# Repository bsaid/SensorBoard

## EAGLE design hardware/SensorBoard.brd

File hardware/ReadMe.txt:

ESP32 Sensor board:

Popis desky:
- dvě desky jako sendvič 50 mm * 31 mm * 13 mm
- propojení desek lze využít jako konektor pro připojení dalších periferií
- 3 možnosti bezdrátového připojení + USB

Vlastnosti:
- vlastní LiPoly baterie se správou napájení a nabíjením přes USB
- USB FTDI
- 80 MHz procesor
- micro SD karta standard 3.0 (lze >32 GB)
- 14 pinů pro připojení volitelných periferií, i výstupních (serva, LED, DAC reproduktor)
- Bluetooth 4.0 nebo WiFi připojení, lze v jeden okamžik používat jen jedno
- 433 nebo 868 MHz radio pro komunikaci na vzdálenost do 1.5 km nebo pro komunikaci skrz biologický materiál (tělo koně)
- citlivá elektronika ukrytá uvnitř sendviče
- 2 tlačítka
- 2 SW LED (+ několik HW LED)
- adapter na magnetický USB-C pro lepší utěsnění proti prachu
- možnost připojit senzor srdečního tepu, dechu, saturace krve kyslíkem (po konzultaci s Monet+)

Senzory:
- akcelerometr
- gyroskop
- kompas
- vlhkoměr
- barometr
- teploměr
- externě GPS, instenzita světla, mikrofon

Navíc:
- deska má dostatek senzorů, výkonu na procesoru a vyvedených konektorů na to, aby šla naprogramovat jako jednoduchý autopilot
- návrh jsem zamýšlel i jako univerzální desku pro vývoj na ESP32 procesorech s některými senzory jako bonus
- 2x DAC (třeba pro příjem a přehrání zvuku)

Problémy během návrhu:
- dostatečně malá deska, která nebude zvířeti zavazet
- chybějící kondenzátor na pinu EN způsoboval nepředvídatelné chování a občas úplnou nefunkčnost procesoru ESP32
- těžko sehnatelná ručně pájitelná pouzdra senzorů
- výběr vhodného čipu pro správu napájení, stále slabé místo, nevyzkoušené předem
- komunikace s firmou a získání relevantních informací a požadavků

Seznam součástek je v samostatném souboru.
Původní zadání a high-level požadavky jsou v samostatném souboru.
Všechny použité součástky jsou uloženy jako samostatné knihovny ve složce lib.

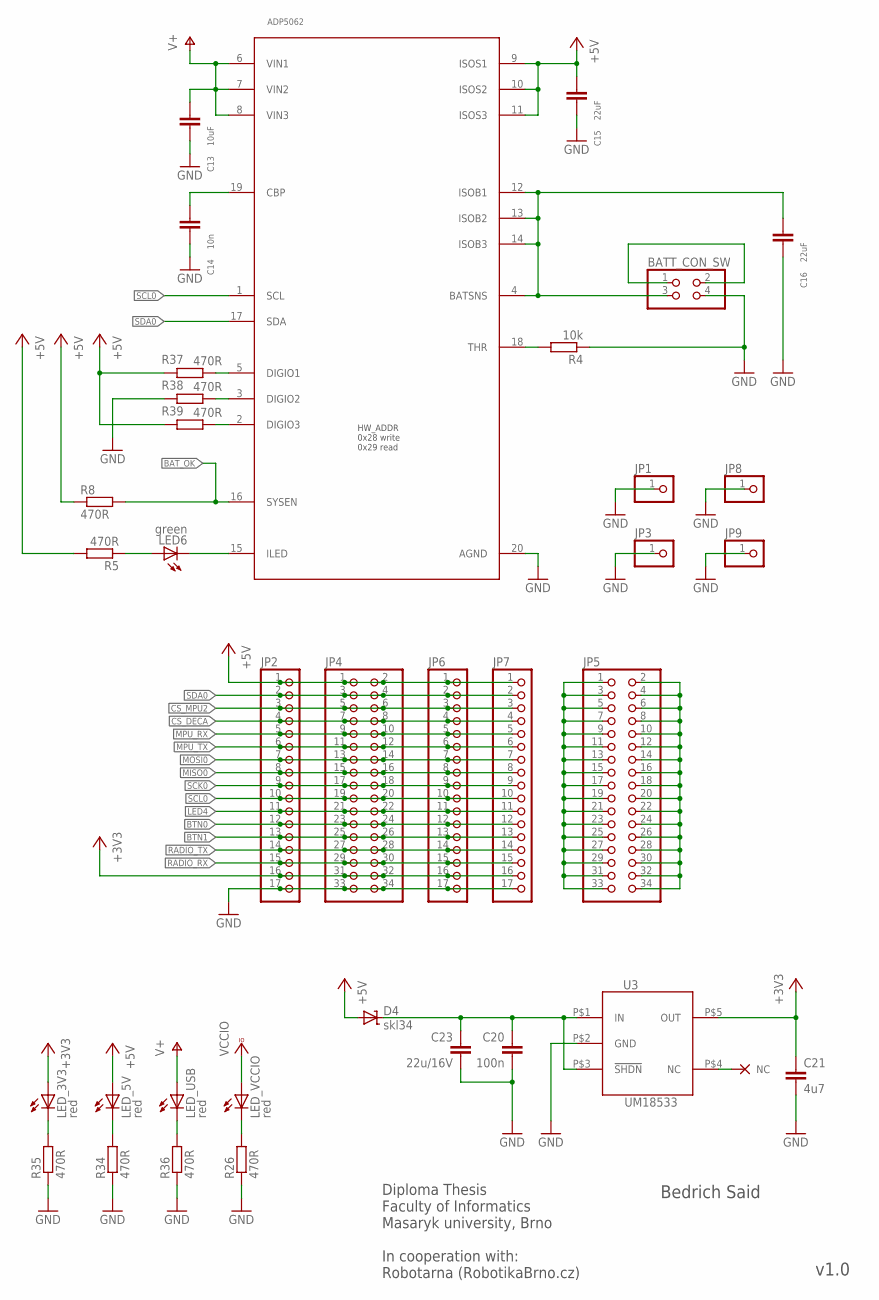
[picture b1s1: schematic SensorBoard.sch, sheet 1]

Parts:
BATT_CON_SW: PINHD-2X2; 2X02
C13: 10uF; C1206
C14: 10n; C0603
C15, C16: 22uF; C1206
C20: 100n; C0603
C21: 4u7; C0603
C23: 22u/16V; C1206
CHARGER: ADP5062; QFN50P400X400X80-21N
D4: skl34; SOD123
JP1, JP3, JP8, JP9: PINHD-1X1; 1X01
JP2, JP6, JP7: PINHD-1X17; 1X17
JP4, JP5: PINHD-2X17; 2X17
LED6: green; CHIPLED_0603
LED_3V3, LED_5V: red; CHIPLED_0603
LED_USB: red; CHIPLED_0603
LED_VCCIO: red; CHIPLED_0603
R4: 10k; R0603
R5, R8, R26, R34, R35, R36, R37, R38, R39: 470R; R0603
U3: UM18533; SOT23-5

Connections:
5V->3V3: C20.1, C23.1, D4.C, U3.P$1 (IN), U3.P$3 (!SHDN)
+3V3: C21.1, JP2.16, JP4.31, JP4.32, JP6.16, JP7.16, LED_3V3.A, U3.P$5 (OUT); also elsewhere on the board
+5V: C15.1, CHARGER.9 (ISOS1), CHARGER.10 (ISOS2), CHARGER.11 (ISOS3), D4.A, JP2.1, JP4.1, JP4.2, JP6.1, JP7.1, LED_5V.A, R5.2, R8.1, R37.2, R39.2; also elsewhere on the board
BAT_OK: CHARGER.16 (SYSEN), R8.2; also elsewhere on the board
BTN0: JP2.12, JP4.23, JP4.24, JP6.12, JP7.12; also elsewhere on the board
BTN1: JP2.13, JP4.25, JP4.26, JP6.13, JP7.13; also elsewhere on the board
CS_DECA: JP2.4, JP4.7, JP4.8, JP6.4, JP7.4; also elsewhere on the board
CS_MPU2: JP2.3, JP4.5, JP4.6, JP6.3, JP7.3; also elsewhere on the board
GND: BATT_CON_SW.4, C13.2, C14.2, C15.2, C16.2, C20.2, C21.2, C23.2, CHARGER.20 (AGND), JP1.1, JP2.17, JP3.1, JP4.33, JP4.34, JP6.17, JP7.17, JP8.1, JP9.1, R4.1, R26.1, R34.1, R35.1, R36.1, R38.2, U3.P$2 (GND); also elsewhere on the board
LED4: JP2.11, JP4.21, JP4.22, JP6.11, JP7.11; also elsewhere on the board
LED_3V3: LED_VCCIO.C, R26.2
LED_3V3_USB: LED_USB.C, R36.2
LED_3V3_USB1: LED_3V3.C, R35.2
LED_3V4: LED_5V.C, R34.2
MISO0: JP2.8, JP4.15, JP4.16, JP6.8, JP7.8; also elsewhere on the board
MOSI0: JP2.7, JP4.13, JP4.14, JP6.7, JP7.7; also elsewhere on the board
MPU_RX: JP2.5, JP4.9, JP4.10, JP6.5, JP7.5; also elsewhere on the board
MPU_TX: JP2.6, JP4.11, JP4.12, JP6.6, JP7.6; also elsewhere on the board
unnamed: JP5.1, JP5.3, JP5.5, JP5.7, JP5.9, JP5.11, JP5.13, JP5.15, JP5.17, JP5.19, JP5.21, JP5.23, JP5.25, JP5.27, JP5.29, JP5.31, JP5.33
unnamed: BATT_CON_SW.3, C16.1, CHARGER.4 (BATSNS), CHARGER.12 (ISOB1), CHARGER.13 (ISOB2), CHARGER.14 (ISOB3)
unnamed: BATT_CON_SW.1, BATT_CON_SW.2
unnamed: CHARGER.18 (THR), R4.2
unnamed: CHARGER.15 (ILED), LED6.C
unnamed: C14.1, CHARGER.19 (CBP)
unnamed: LED6.A, R5.1
unnamed: CHARGER.5 (DIGIO1), R37.1
unnamed: CHARGER.3 (DIGIO2), R38.1
unnamed: CHARGER.2 (DIGIO3), R39.1
unnamed: JP5.2, JP5.4, JP5.6, JP5.8, JP5.10, JP5.12, JP5.14, JP5.16, JP5.18, JP5.20, JP5.22, JP5.24, JP5.26, JP5.28, JP5.30, JP5.32, JP5.34
RADIO_RX: JP2.15, JP4.29, JP4.30, JP6.15, JP7.15; also elsewhere on the board
RADIO_TX: JP2.14, JP4.27, JP4.28, JP6.14, JP7.14; also elsewhere on the board
SCK0: JP2.9, JP4.17, JP4.18, JP6.9, JP7.9; also elsewhere on the board
SCL0: CHARGER.1 (SCL), JP2.10, JP4.19, JP4.20, JP6.10, JP7.10; also elsewhere on the board
SDA0: CHARGER.17 (SDA), JP2.2, JP4.3, JP4.4, JP6.2, JP7.2; also elsewhere on the board
U2_NC1: U3.P$4 (NC)
V+: C13.1, CHARGER.6 (VIN1), CHARGER.7 (VIN2), CHARGER.8 (VIN3), LED_USB.A; also elsewhere on the board
VCCIO: LED_VCCIO.A; also elsewhere on the board

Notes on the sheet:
Diploma Thesis Faculty of Informatics Masaryk university, Brno In cooperation with: Robotarna (RobotikaBrno.cz)
Bedrich Said
v1.0
HW_ADDR 0x28 write 0x29 read

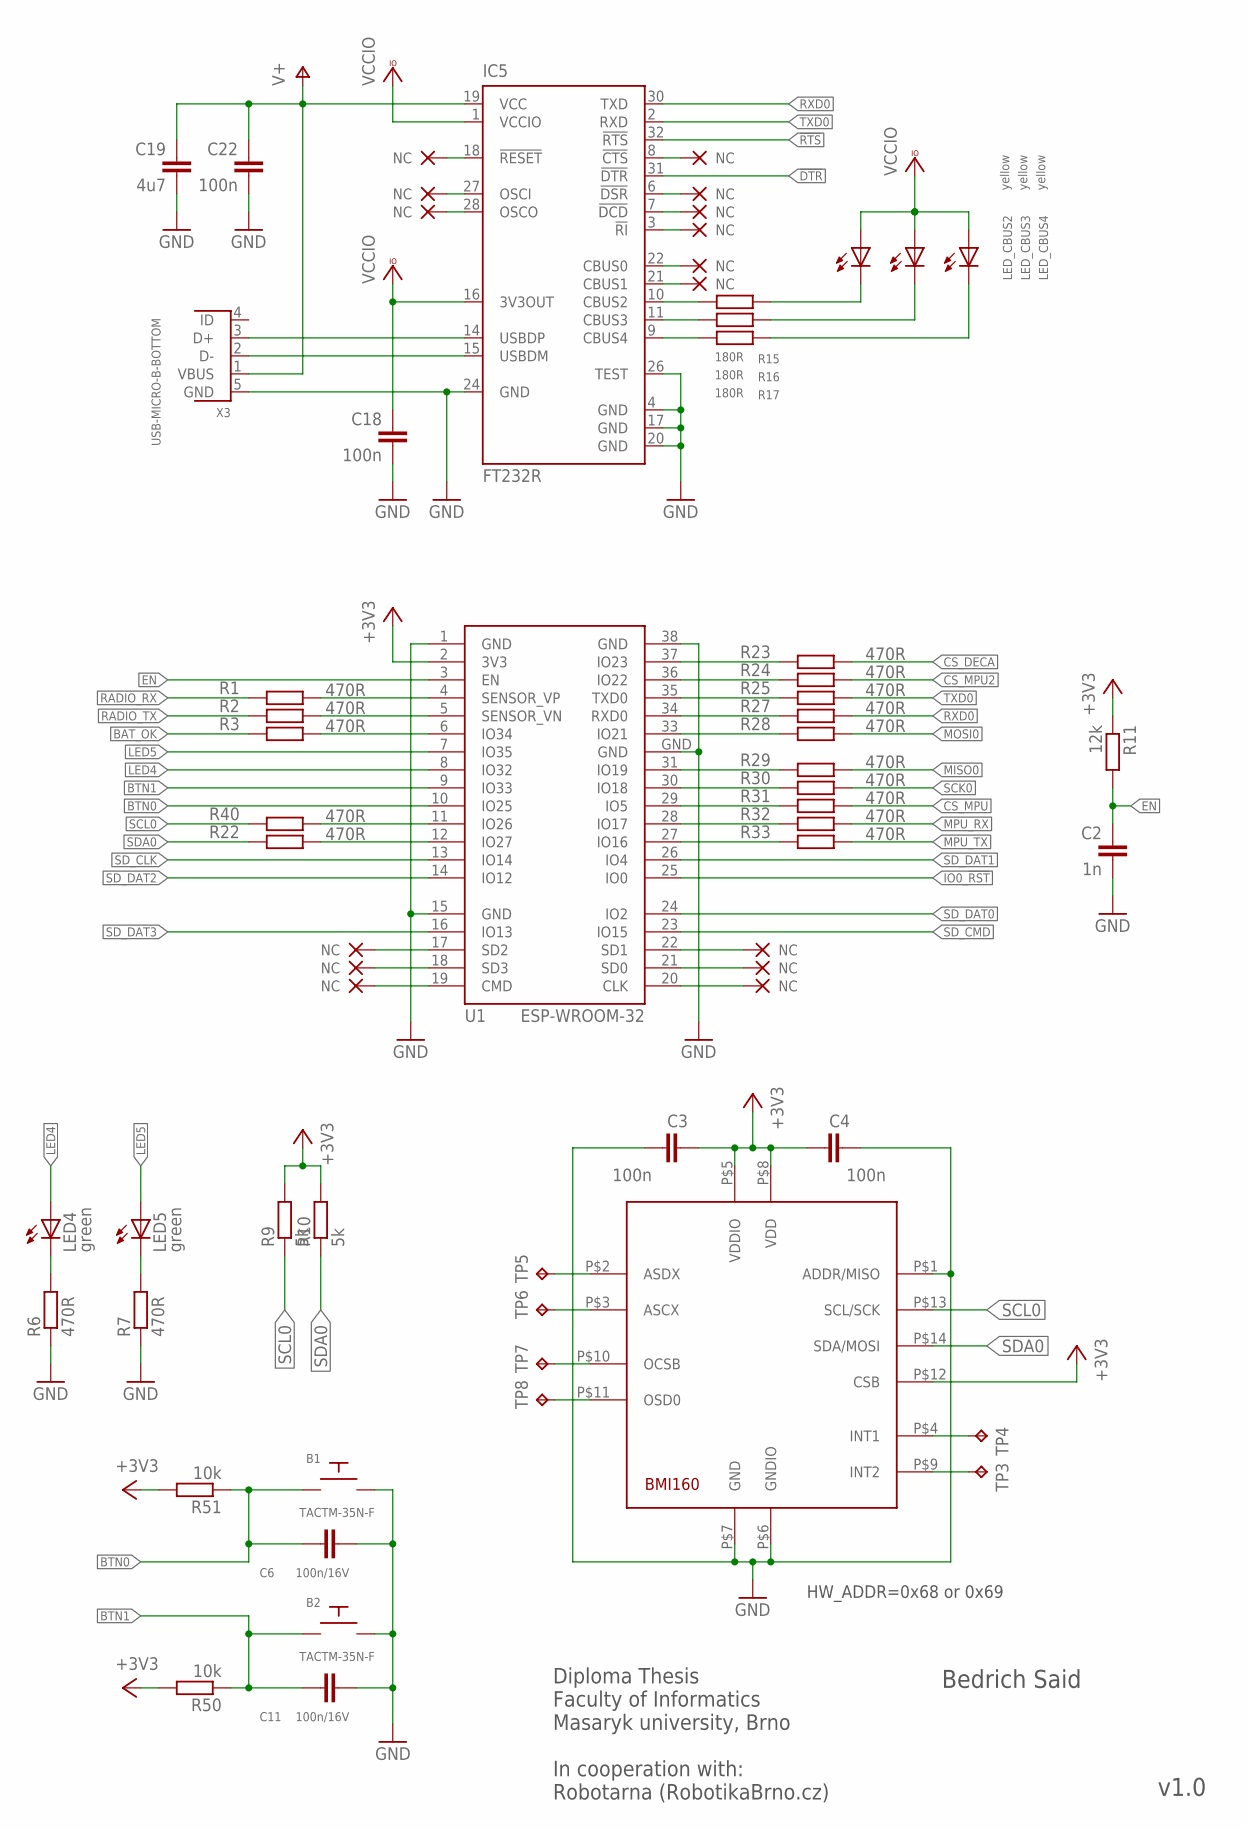
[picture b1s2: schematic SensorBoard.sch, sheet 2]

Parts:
B1, B2: TACTM-35N-F
C2: 1n; C0603
C3, C4, C18, C22: 100n; C0603
C6, C11: 100n/16V; C0603
C19: 4u7; C0603
IC5: FT232R; QFN32_LONG_PADS
LED4, LED5: green; CHIPLED_0603
LED_CBUS2, LED_CBUS3, LED_CBUS4: yellow; CHIP-LED0603
R1, R2, R3, R6, R7, R22, R23, R24, R25, R27, R28, R29, R30, R31, R32, R33, R40: 470R; R0603
R9, R10: 5k; R0603
R11: 12k; R0603
R15, R16, R17: 180R; R0603
R50, R51: 10k; R0603
TP3, TP4, TP5, TP6, TP7, TP8: TPTP08SQ; TP08SQ
U1: ESP-WROOM-32
U$3: BMI160LGA14; LGA14-BMI160
X3: USB-MICRO-B-BOTTOM; USB-MICRO-B-BOTTOM-MOLEX

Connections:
!DTR: IC5.31 (!DTR); also elsewhere on the board
!RTS: IC5.32 (!RTS); also elsewhere on the board
+3V3: C3.2, C4.1, R9.2, R10.2, R11.1, R50.2, R51.2, U1.2 (3V3), U$3.P$5 (VDDIO), U$3.P$8 (VDD), U$3.P$12 (CSB); also elsewhere on the board
BAT_OK: R3.2; also elsewhere on the board
BTN0: B1.P$4, C6.2, R51.1, U1.10 (IO25); also elsewhere on the board
BTN1: B2.P$4, C11.2, R50.1, U1.9 (IO33); also elsewhere on the board
CBUS2: IC5.10 (CBUS2), R15.2
CBUS2_LED: LED_CBUS2.C, R15.1
CBUS3: IC5.11 (CBUS3), R16.2
CBUS3_LED: LED_CBUS3.C, R16.1
CBUS4: IC5.9 (CBUS4), R17.2
CBUS4_LED: LED_CBUS4.C, R17.1
CS_DECA: R23.1; also elsewhere on the board
CS_MPU: R31.1; also elsewhere on the board
CS_MPU2: R24.1; also elsewhere on the board
EN: C2.1, R11.2, U1.3 (EN); also elsewhere on the board
GND: B1.P$2, B2.P$2, C2.2, C3.1, C4.2, C6.1, C11.1, C18.2, C19.2, C22.2, IC5.4 (GND), IC5.17 (GND), IC5.20 (GND), IC5.24 (GND), IC5.26 (TEST), R6.1, R7.1, U1.1 (GND), U1.15 (GND), U1.38 (GND), U1.GND, U$3.P$1 (ADDR/MISO), U$3.P$6 (GNDIO), U$3.P$7 (GND), X3.5 (GND); also elsewhere on the board
IO0_!RST: U1.25 (IO0); also elsewhere on the board
IO5: R31.2, U1.29 (IO5)
IO16: R33.2, U1.27 (IO16)
IO17: R32.2, U1.28 (IO17)
IO18: R30.2, U1.30 (IO18)
IO19: R29.2, U1.31 (IO19)
IO21: R28.2, U1.33 (IO21)
IO22: R24.2, U1.36 (IO22)
IO23: R23.2, U1.37 (IO23)
IO26: R40.1, U1.11 (IO26)
IO27: R22.1, U1.12 (IO27)
IO34: R3.1, U1.6 (IO34)
LED4: LED4.A, U1.8 (IO32); also elsewhere on the board
LED5: LED5.A, U1.7 (IO35)
LED_3V1: LED4.C, R6.2
LED_3V2: LED5.C, R7.2
MISO0: R29.1; also elsewhere on the board
MOSI0: R28.1; also elsewhere on the board
MPU_RX: R32.1; also elsewhere on the board
MPU_TX: R33.1; also elsewhere on the board
unnamed: TP5.TP, U$3.P$2 (ASDX)
unnamed: TP6.TP, U$3.P$3 (ASCX)
unnamed: TP7.TP, U$3.P$10 (OCSB)
unnamed: TP8.TP, U$3.P$11 (OSD0)
unnamed: TP4.TP, U$3.P$4 (INT1)
unnamed: TP3.TP, U$3.P$9 (INT2)
RADIO_RX: R1.2; also elsewhere on the board
RADIO_TX: R2.2; also elsewhere on the board
RXD0: IC5.30 (TXD), R27.1
RXD0_: R27.2, U1.34 (RXD0)
SCK0: R30.1; also elsewhere on the board
SCL0: R9.1, R40.2, U$3.P$13 (SCL/SCK); also elsewhere on the board
SDA0: R10.1, R22.2, U$3.P$14 (SDA/MOSI); also elsewhere on the board
SD_CLK: U1.13 (IO14); also elsewhere on the board
SD_CMD: U1.23 (IO15); also elsewhere on the board
SD_DAT0: U1.24 (IO2); also elsewhere on the board
SD_DAT1: U1.26 (IO4); also elsewhere on the board
SD_DAT2: U1.14 (IO12); also elsewhere on the board
SD_DAT3: U1.16 (IO13); also elsewhere on the board
SENSOR_VN_: R2.1, U1.5 (SENSOR_VN)
SENSOR_VP_: R1.1, U1.4 (SENSOR_VP)
TXD0: IC5.2 (RXD), R25.1
TXD0_: R25.2, U1.35 (TXD0)
USBDM: IC5.15 (USBDM), X3.2 (D-)
USBDP: IC5.14 (USBDP), X3.3 (D+)
V+: C19.1, C22.1, IC5.19 (VCC), X3.1 (VBUS); also elsewhere on the board
VCCIO: C18.1, IC5.1 (VCCIO), IC5.16 (3V3OUT), LED_CBUS2.A, LED_CBUS3.A, LED_CBUS4.A; also elsewhere on the board

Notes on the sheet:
Diploma Thesis Faculty of Informatics Masaryk university, Brno In cooperation with: Robotarna (RobotikaBrno.cz)
Bedrich Said
v1.0
HW_ADDR=0x68 or 0x69

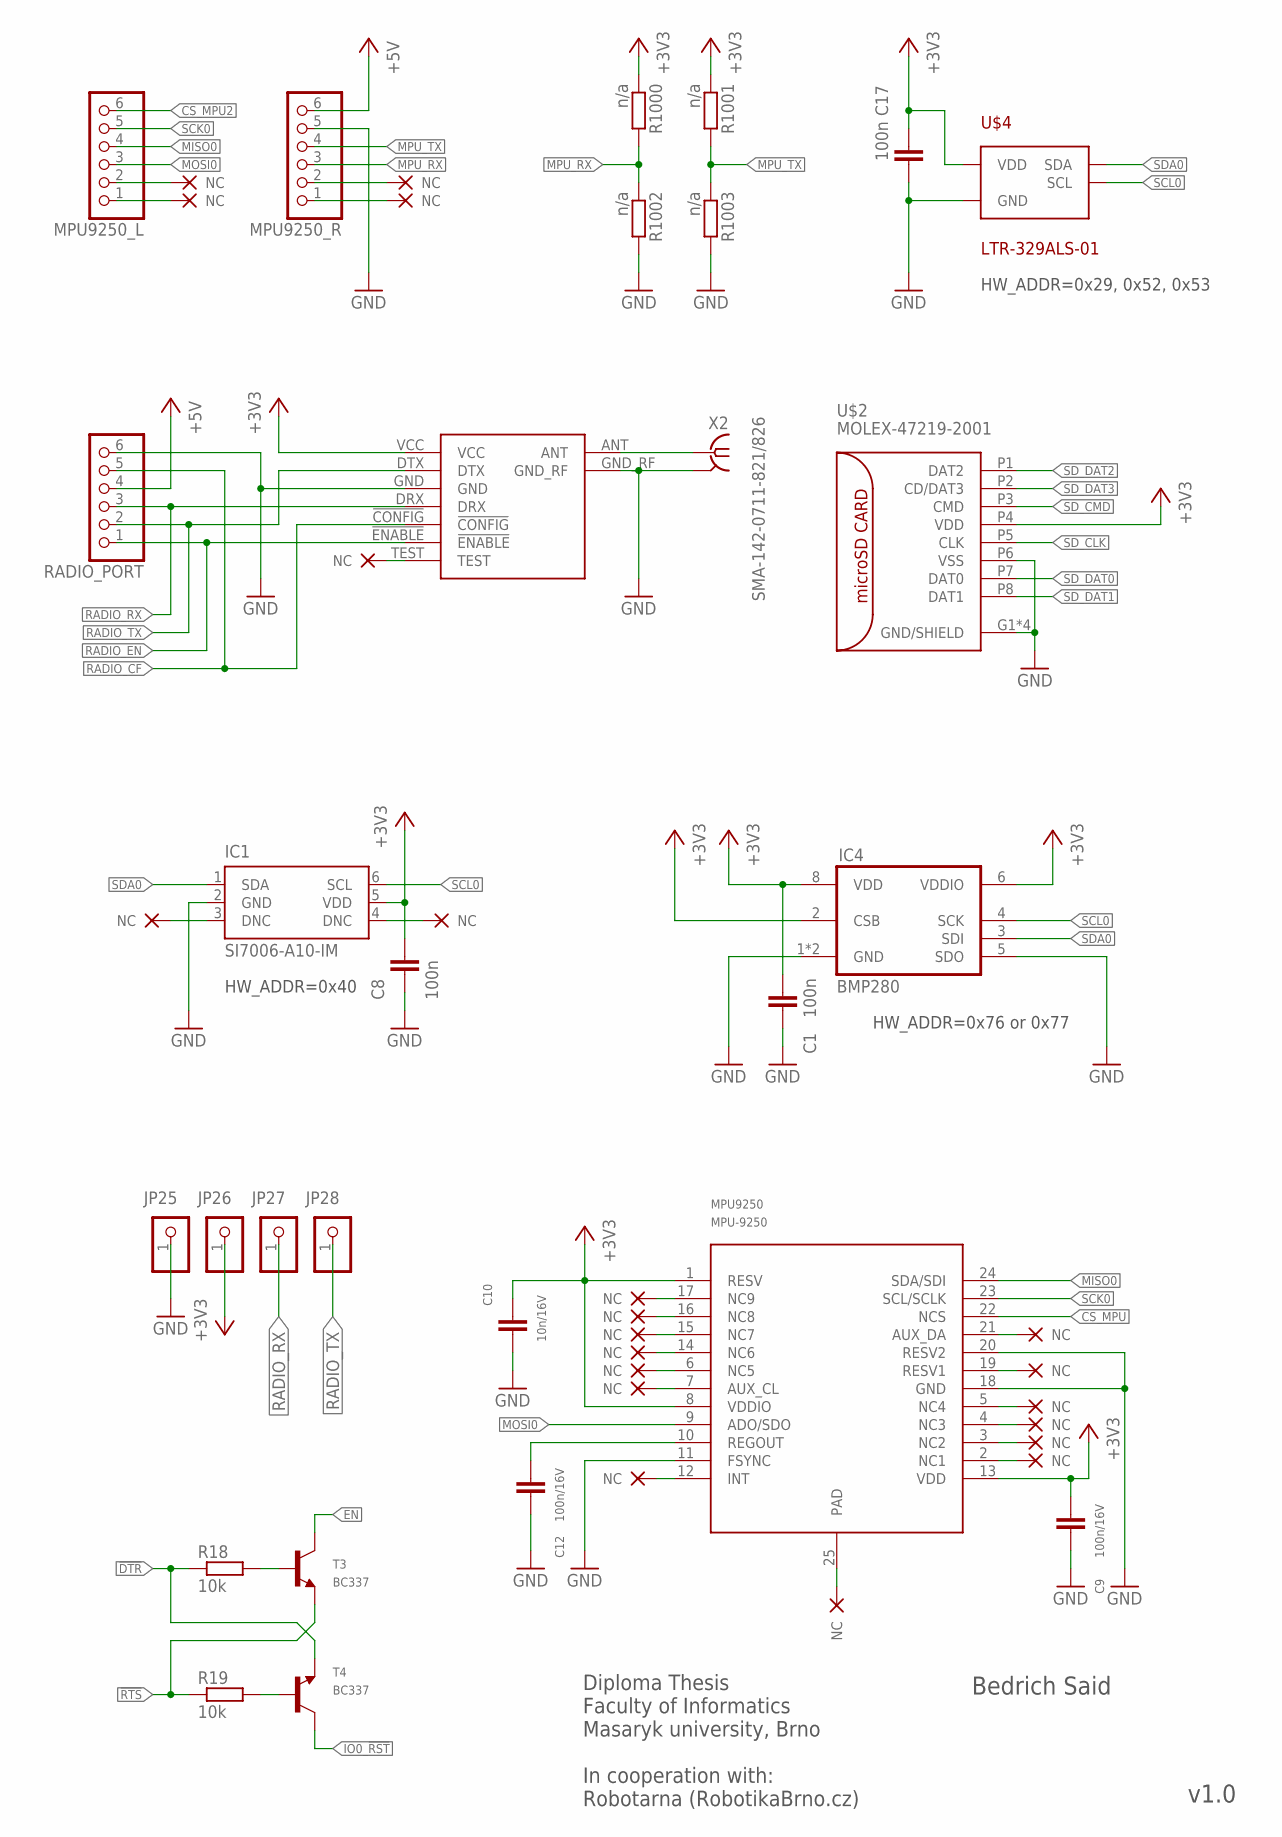
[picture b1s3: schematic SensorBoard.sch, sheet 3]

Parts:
C1, C8, C17: 100n; C0603
C9, C12: 100n/16V; C0603
C10: 10n/16V; C0603
IC1: SI7006-A10-IM; DFN6-3X3
IC4: BMP280
JP25, JP26, JP27, JP28: PINHD-1X1; 1X01
MPU9250: MPU-9250; LEAD-QFN24
MPU9250_L, MPU9250_R: PINHD-1X6; 1X06
R18, R19: 10k; R0603
R1000, R1001, R1002, R1003: n/a; R0603
RADIO_PORT: PINHD-1X6; 1X06
T3, T4: BC337; SOT23
U$1: HM-TRP
U$2: MOLEX-47219-2001; MOLEX:47219-2001
U$4: LTR-329ALS-01; CHIPLED-4
X2: SMA-142-0711-821/826; J502-ND-142-0711-821/826

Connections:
!DTR: R18.1, T4.2 (E); also elsewhere on the board
!DTR_B: R18.2, T3.1 (B)
!RTS: R19.1, T3.2 (E); also elsewhere on the board
!RTS_B: R19.2, T4.1 (B)
+3V3: C1.1, C8.1, C9.1, C10.1, C17.2, IC1.5 (VDD), IC4.2 (CSB), IC4.6 (VDDIO), IC4.8 (VDD), JP26.1, MPU9250.1 (RESV), MPU9250.8 (VDDIO), MPU9250.13 (VDD), R1000.1, R1001.1, U$1.VCC, U$2.P4 (VDD), U$4.1 (VDD); also elsewhere on the board
+5V: MPU9250_R.6, RADIO_PORT.4; also elsewhere on the board
CS_MPU: MPU9250.22 (NCS); also elsewhere on the board
CS_MPU2: MPU9250_L.6; also elsewhere on the board
EN: T3.3 (C); also elsewhere on the board
GND: C1.2, C8.2, C9.2, C10.2, C12.2, C17.1, IC1.2 (GND), IC4.1 (GND), IC4.5 (SDO), IC4.7 (GND), JP25.1, MPU9250.11 (FSYNC), MPU9250.18 (GND), MPU9250.20 (RESV2), MPU9250_R.5, R1002.2, R1003.2, RADIO_PORT.6, U$1.GND, U$1.GND_RF, U$2.G1 (GND/SHIELD), U$2.G2 (GND/SHIELD), U$2.G3 (GND/SHIELD), U$2.G4 (GND/SHIELD), U$2.P6 (VSS), U$4.2 (GND), X2.G@1 (2), X2.G@2 (2), X2.G@3 (2), X2.G@4 (2); also elsewhere on the board
IO0_!RST: T4.3 (C); also elsewhere on the board
MISO0: MPU9250.24 (SDA/SDI), MPU9250_L.4; also elsewhere on the board
MOSI0: MPU9250.9 (ADO/SDO), MPU9250_L.3; also elsewhere on the board
MPU_RX: MPU9250_R.3, R1000.2, R1002.1; also elsewhere on the board
MPU_TX: MPU9250_R.4, R1001.2, R1003.1; also elsewhere on the board
unnamed: C12.1, MPU9250.10 (REGOUT)
unnamed: U$1.ANT, X2.1
RADIO_CF: RADIO_PORT.5, U$1.!CONFIG
RADIO_EN: RADIO_PORT.1, U$1.!ENABLE
RADIO_RX: JP27.1, RADIO_PORT.3, U$1.DRX; also elsewhere on the board
RADIO_TX: JP28.1, RADIO_PORT.2, U$1.DTX; also elsewhere on the board
SCK0: MPU9250.23 (SCL/SCLK), MPU9250_L.5; also elsewhere on the board
SCL0: IC1.6 (SCL), IC4.4 (SCK), U$4.4 (SCL); also elsewhere on the board
SDA0: IC1.1 (SDA), IC4.3 (SDI), U$4.3 (SDA); also elsewhere on the board
SD_CLK: U$2.P5 (CLK); also elsewhere on the board
SD_CMD: U$2.P3 (CMD); also elsewhere on the board
SD_DAT0: U$2.P7 (DAT0); also elsewhere on the board
SD_DAT1: U$2.P8 (DAT1); also elsewhere on the board
SD_DAT2: U$2.P1 (DAT2); also elsewhere on the board
SD_DAT3: U$2.P2 (CD/DAT3); also elsewhere on the board

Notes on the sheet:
HW_ADDR=0x40
HW_ADDR=0x76 or 0x77
HW_ADDR=0x29, 0x52, 0x53
Diploma Thesis Faculty of Informatics Masaryk university, Brno In cooperation with: Robotarna (RobotikaBrno.cz)
Bedrich Said
v1.0

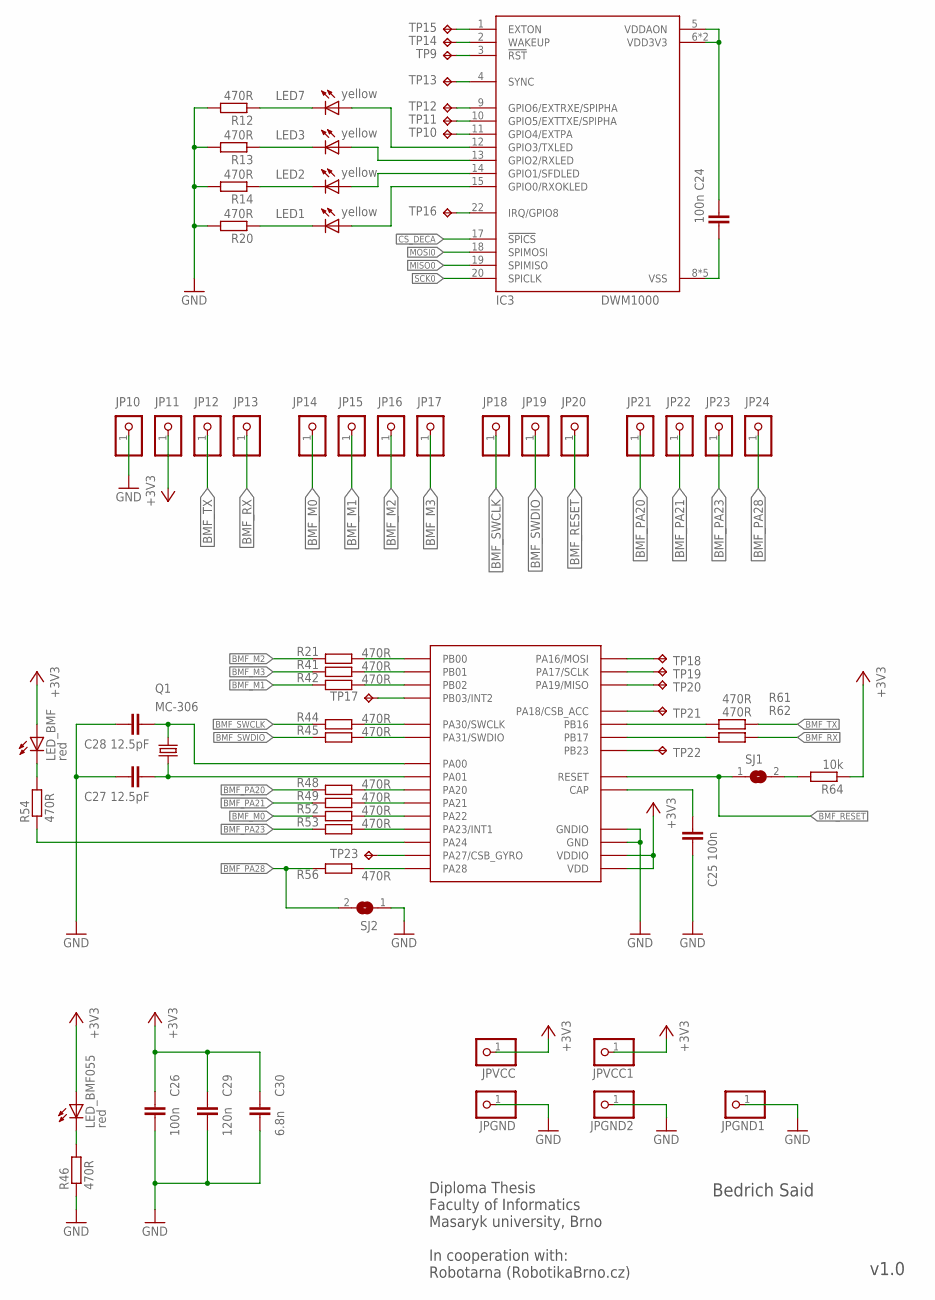
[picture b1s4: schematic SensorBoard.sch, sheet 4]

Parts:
C24, C25, C26: 100n; C0603
C27, C28: 12.5pF; C0603
C29: 120n; C0603
C30: 6.8n; C0603
IC3: DWM1000
JP10, JP11, JP12, JP13, JP14, JP15, JP16, JP17, JP18, JP19, JP20, JP21, JP22, JP23, JP24: PINHD-1X1; 1X01
JPGND, JPGND1, JPGND2: PINHD-1X1; 1X01
JPVCC, JPVCC1: PINHD-1X1; 1X01
LED1, LED2, LED3, LED7: yellow; CHIPLED_0603
LED_BMF, LED_BMF055: red; CHIPLED_0603
Q1: MC-306
R12, R13, R14, R20, R21, R41, R42, R44, R45, R46, R48, R49, R52, R53, R54, R56, R61, R62: 470R; R0603
R64: 10k; R0603
SJ1, SJ2: SJ
TP9, TP10, TP11, TP12, TP13, TP14, TP15, TP22, TP23: TPTP15SQ; TP15SQ
TP16: TPTP20SQ; TP20SQ
TP17, TP18, TP19, TP20, TP21: TPTP08SQ; TP08SQ
U$5: BMF055; LGA-28

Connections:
+3V3: C26.1, C29.1, C30.1, JP11.1, JPVCC.1, JPVCC1.1, LED_BMF.A, LED_BMF055.A, R64.1, U$5.P$3 (VDD), U$5.P$28 (VDDIO); also elsewhere on the board
BMF_M0: JP14.1, R52.2
BMF_M1: JP15.1, R42.2
BMF_M2: JP16.1, R21.2
BMF_M3: JP17.1, R41.2
BMF_PA20: JP21.1, R48.2
BMF_PA21: JP22.1, R49.2
BMF_PA23: JP23.1, R53.2
BMF_PA28: JP24.1, R56.2, SJ2.2
BMF_RESET: JP20.1, SJ1.1, U$5.P$11 (RESET)
BMF_RX: JP13.1, R62.1
BMF_SWCLK: JP18.1, R44.2
BMF_SWDIO: JP19.1, R45.2
BMF_TX: JP12.1, R61.1
CS_DECA: IC3.17 (!SPICS); also elsewhere on the board
GND: C25.2, C26.2, C27.2, C28.2, C29.2, C30.2, JP10.1, JPGND.1, JPGND1.1, JPGND2.1, R12.2, R13.2, R14.2, R20.2, R46.1, SJ2.1, U$5.P$2 (GND), U$5.P$25 (GNDIO); also elsewhere on the board
LED_3V3_USB2: LED_BMF055.C, R46.2
MISO0: IC3.19 (SPIMISO); also elsewhere on the board
MOSI0: IC3.18 (SPIMOSI); also elsewhere on the board
unnamed: R21.1, U$5.P$6 (PB00)
unnamed: LED1.C, R20.1
unnamed: LED2.C, R14.1
unnamed: LED3.C, R13.1
unnamed: IC3.22 (IRQ/GPIO8), TP16.TP
unnamed: R41.1, U$5.P$5 (PB01)
unnamed: C24.1, IC3.8 (VSS), IC3.16 (VSS), IC3.21 (VSS), IC3.23 (VSS), IC3.24 (VSS)
unnamed: C24.2, IC3.5 (VDDAON), IC3.6 (VDD3V3), IC3.7 (VDD3V3)
unnamed: R42.1, U$5.P$4 (PB02)
unnamed: LED7.C, R12.1
unnamed: IC3.12 (GPIO3/TXLED), LED7.A
unnamed: IC3.13 (GPIO2/RXLED), LED3.A
unnamed: IC3.14 (GPIO1/SFDLED), LED2.A
unnamed: IC3.15 (GPIO0/RXOKLED), LED1.A
unnamed: IC3.11 (GPIO4/EXTPA), TP10.TP
unnamed: IC3.3 (!RST), TP9.TP
unnamed: IC3.10 (GPIO5/EXTTXE/SPIPHA), TP11.TP
unnamed: IC3.9 (GPIO6/EXTRXE/SPIPHA), TP12.TP
unnamed: IC3.4 (SYNC), TP13.TP
unnamed: IC3.2 (WAKEUP), TP14.TP
unnamed: IC3.1 (EXTON), TP15.TP
unnamed: TP17.TP, U$5.P$1 (PB03/INT2)
unnamed: R44.1, U$5.P$8 (PA30/SWCLK)
unnamed: R45.1, U$5.P$7 (PA31/SWDIO)
unnamed: C28.1, Q1.4 (2), U$5.P$27 (PA00)
unnamed: C27.1, Q1.1, U$5.P$26 (PA01)
unnamed: R48.1, U$5.P$18 (PA20)
unnamed: R49.1, U$5.P$17 (PA21)
unnamed: R52.1, U$5.P$16 (PA22)
unnamed: R53.1, U$5.P$15 (PA23/INT1)
unnamed: R54.1, U$5.P$14 (PA24)
unnamed: TP23.TP, U$5.P$12 (PA27/CSB_GYRO)
unnamed: R56.1, U$5.P$10 (PA28)
unnamed: TP18.TP, U$5.P$24 (PA16/MOSI)
unnamed: TP19.TP, U$5.P$23 (PA17/SCLK)
unnamed: TP20.TP, U$5.P$21 (PA19/MISO)
unnamed: TP21.TP, U$5.P$22 (PA18/CSB_ACC)
unnamed: R61.2, U$5.P$20 (PB16)
unnamed: R62.2, U$5.P$19 (PB17)
unnamed: TP22.TP, U$5.P$13 (PB23)
unnamed: LED_BMF.C, R54.2
unnamed: C25.1, U$5.P$9 (CAP)
unnamed: R64.2, SJ1.2
SCK0: IC3.20 (SPICLK); also elsewhere on the board

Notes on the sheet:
Diploma Thesis Faculty of Informatics Masaryk university, Brno In cooperation with: Robotarna (RobotikaBrno.cz)
Bedrich Said
v1.0

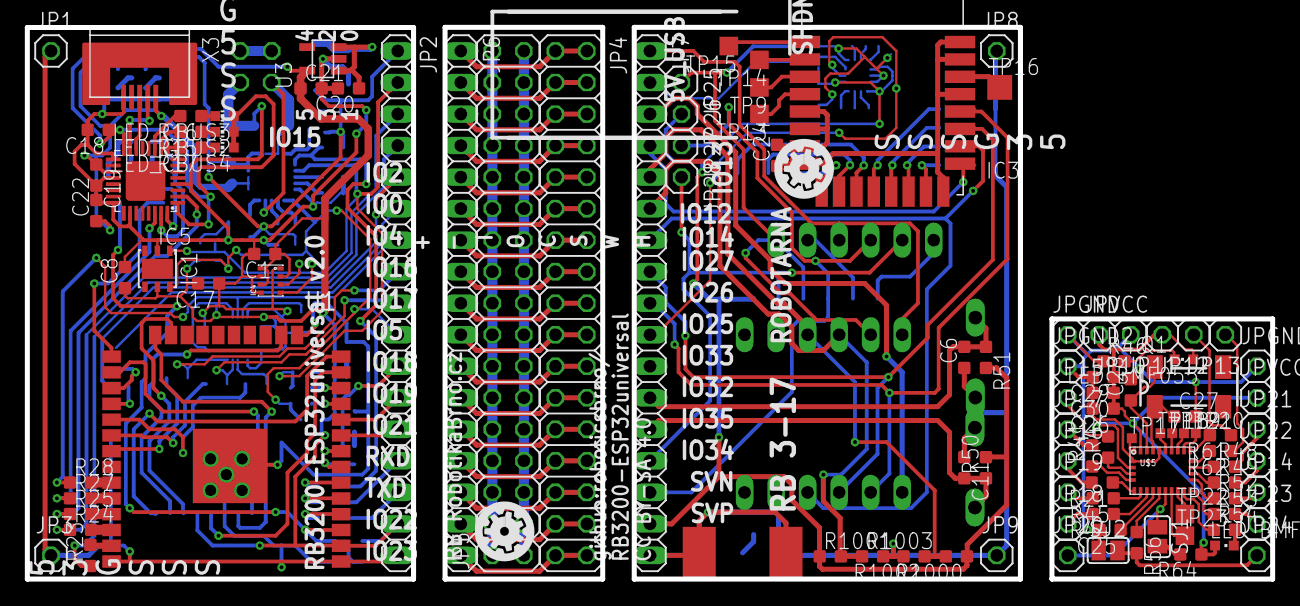
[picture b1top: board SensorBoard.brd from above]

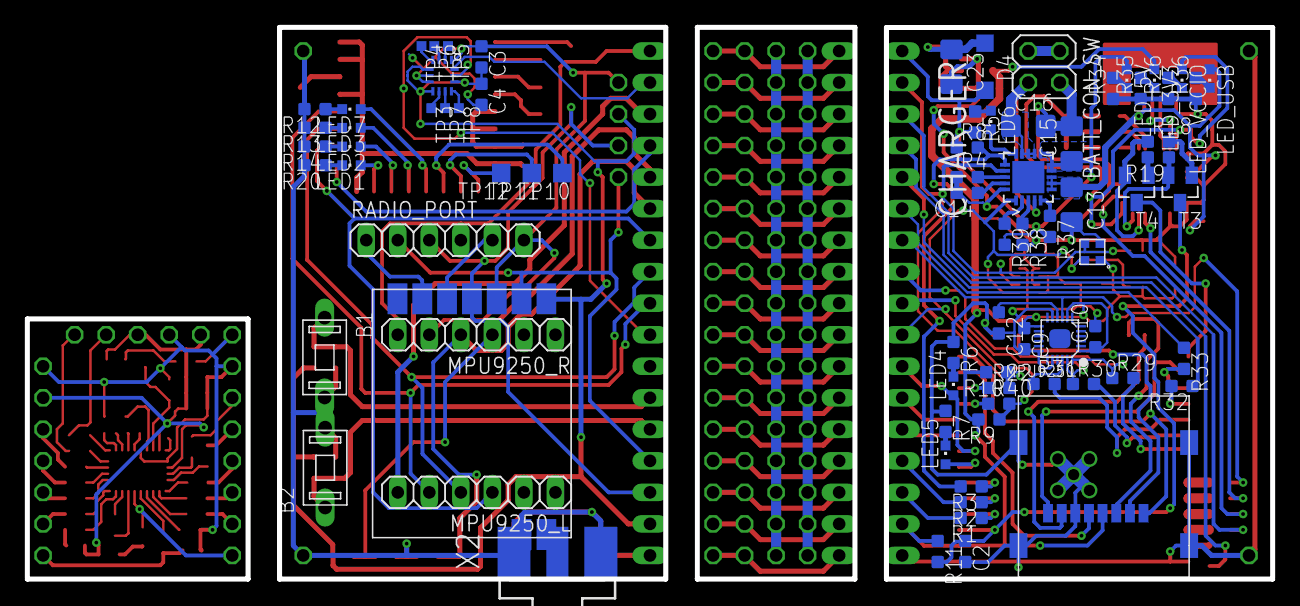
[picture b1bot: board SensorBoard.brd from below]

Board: 2 copper layers, 100.3 x 44.5 mm, 185 parts (78 on the bottom side), 144 nets.

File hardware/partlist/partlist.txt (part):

Partlist

Exported from SensorBoard.brd at 7/30/2017 3:47 PM

EAGLE Version 7.5.0 Copyright (c) 1988-2015 CadSoft

Assembly variant: 

Part        Value                Package                  Library           Position (mm)         Orientation

B1          TACTM-35N-F          TACTM-35N-F              TACTM-35N-F       (76.35875 17.859375)  MR270
B2          TACTM-35N-F          TACTM-35N-F              TACTM-35N-F       (76.35875 8.969375)   MR90
BATT_CON_SW                      2X02                     pinhead           (18.415 41.275)       MR270
C1          100n                 C0603                    rcl_upravena      (19.129375 26.19375)  R180
C2          1n                   C0603                    rcl_upravena      (24.765 2.2225)       MR270
C3          100n                 C0603                    rcl_upravena      (63.738125 42.06875)  MR270
C4          100n                 C0603                    rcl_upravena      (63.738125 39.0525)   MR270
C6          100n/16V             C0603                    rcl_upravena      (75.485625 17.859375) R90
C8          100n                 C0603                    rcl_upravena      (7.858125 24.28875)   R90
C9          100n/16V             C0603                    rcl_upravena      (20.0025 19.3675)     MR270
C10         10n/16V              C0603                    rcl_upravena      (14.2875 19.52625)    MR90
C11         100n/16V             C0603                    rcl_upravena      (75.485625 8.969375)  R270
C12         100n/16V             C0603                    rcl_upravena      (22.06625 20.6375)    MR270
C13         10uF                 C1206                    rcl_upravena      (16.1925 30.1625)     MR270
C14         10n                  C0603                    rcl_upravena      (24.60625 31.115)     MR180
C15         22uF                 C1206                    rcl_upravena      (16.1925 35.08375)    MR90
C16         22uF                 C1206                    rcl_upravena      (19.685 36.5125)      MR0
C17         100n                 C0603                    rcl_upravena      (14.605 23.8125)      R180
C18         100n                 C0603                    rcl_upravena      (5.715 36.195)        R180
C19         4u7                  C0603                    rcl_upravena      (5.55625 32.54375)    R270
C20         100n                 C0603                    rcl_upravena      (25.87625 39.52875)   R180
C21         4u7                  C0603                    rcl_upravena      (22.86 39.52875)      R0
C22         100n                 C0603                    rcl_upravena      (5.55625 29.68625)    R90
C23         22u/16V              C1206                    rcl_upravena      (25.87625 41.275)     MR270
C24         100n                 C0603                    rcl_upravena      (60.404375 34.13125)  R90
C25         100n                 C0603                    rcl_upravena      (87.233125 3.96875)   R180
C26         100n                 C0603                    rcl_upravena      (86.6775 13.731875)   R180
C27         12.5pF               C0603                    rcl_upravena      (93.265625 13.096875) R0
C28         12.5pF               C0603                    rcl_upravena      (88.9 15.24)          R90
C29         120n                 C0603                    rcl_upravena      (86.6775 16.271875)   R180
C30         6.8n                 C0603                    rcl_upravena      (86.6775 15.001875)   R180
CHARGER     ADP5062              QFN50P400X400X80-21N     OMAT_IC           (19.685 32.385)       MR90
D4          skl34                SOD123                   diode             (23.1775 41.275)      MR270
IC1         SI7006-A10-IM        DFN6-3X3                 si70xx            (10.4775 25.003125)   R270
IC3         DWM1000              DWM1000                  decawave          (68.8975 42.465625)   R0
IC4         BMP280               BMP280                   bosch-bmp280      (19.605625 24.050625) R90
IC5         FT232R               QFN32_LONG_PADS          ftdichip_upravena (9.525 32.0675)       R180
JP1                              1X01                     pinhead           (1.905 42.545)        R0
JP2                              1X17                     pinhead           (29.845 22.225)       R270
JP3                              1X01                     pinhead           (1.905 1.905)         R0
JP4                              2X17                     pinhead           (43.815 22.225)       R270
JP5                              2X17                     pinhead           (38.735 22.225)       R90
JP6                              1X17                     pinhead           (34.925 22.225)       R270
JP7                              1X17                     pinhead           (50.165 22.225)       R270
JP8                              1X01                     pinhead           (78.105 42.545)       R0
JP9                              1X01                     pinhead           (78.105 1.905)        R0
JP10                             1X01                     pinhead           (88.9 19.685)         R180
JP11                             1X01                     pinhead           (91.44 19.685)        R180
JP12                             1X01                     pinhead           (93.98 19.685)        R180
JP13                             1X01                     pinhead           (96.52 19.685)        R180
JP14                             1X01                     pinhead           (99.06 6.985)         R0
JP15                             1X01                     pinhead           (83.82 14.605)        R0
JP16                             1X01                     pinhead           (83.82 9.525)         R0
JP17                             1X01                     pinhead           (83.82 12.065)        R0
JP18                             1X01                     pinhead           (83.82 4.445)         R0
JP19                             1X01                     pinhead           (83.82 6.985)         R0
JP20                             1X01                     pinhead           (83.82 1.905)         R0
JP21                             1X01                     pinhead           (99.06 12.065)        R0
JP22                             1X01                     pinhead           (99.06 9.525)         R0
JP23                             1X01                     pinhead           (99.06 4.445)         R0
JP24                             1X01                     pinhead           (99.06 1.905)         R0
JP25                             1X01                     pinhead           (52.705 40.005)       R270
JP26                             1X01                     pinhead           (52.705 37.465)       R270
JP27                             1X01                     pinhead           (52.705 34.925)       R270
JP28                             1X01                     pinhead           (52.705 32.385)       R270
JP30                             1X01                     pinhead           (86.36 19.685)        R0
JP31                             1X01                     pinhead           (99.06 17.145)        R0
JP33                             1X01                     pinhead           (83.82 17.145)        R0
JP34                             1X01                     pinhead           (99.06 14.605)        R0
JP35                             1X01                     pinhead           (83.82 19.685)        R0
LED1        yellow               CHIPLED_0603             led               (74.215625 33.3375)   MR90
LED2        yellow               CHIPLED_0603             led               (74.215625 34.845625) MR90
LED3        yellow               CHIPLED_0603             led               (74.215625 36.35375)  MR90
LED4        green                CHIPLED_0603             led               (25.7175 15.5575)     MR0
LED5        green                CHIPLED_0603             led               (26.3525 10.00125)    MR0
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
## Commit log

2017-11-02 Initial commit.
2017-11-03 Added .gitignore for Eagle and QT.
2017-11-03 Added SensorBoard firmware.
2017-11-03 Added hardware design in Eagle.
2017-11-03 Added LaTeX texts.
2017-11-04 Firmware: Implemented filesystem.
2017-11-06 Firmware: Copied code for WiFi.h from test project.
2017-11-07 Firmware: Implemeted reading ACC + GYR data from MPU9250.
2017-11-08 Firmware: Created Stopwatch in test project.
2017-11-10 Firmware: Stopwatch integrated to main project.
2017-11-12 Added component BMP280, updated esp-idf, logging enabled.
2017-11-13 Added WiFi to test project.
2017-11-13 Deleted module BMP280.
2017-11-13 Added BMP280 component as git submodule.
2017-11-14 Added build target "make clean" and "make all".
2017-11-14 Compiled WiFi at test project.
2017-11-14 Renamed constants in WiFi test project.
2017-11-14 Created test main for WiFi.
2018-02-12 Hello World test update
2018-02-12 Cleaned hardware data.
2018-02-12 Added exported data from hardware layout.
2018-02-12 First update of the thesis text.
2018-02-13 Added manufacturing data.
2018-02-13 Added schematics and board layout to the thesis text.
2018-02-16 Added other text to Hardware, written the first version of Abstract, added Bibliography and Index.
2018-03-06 Merged output to one PDF file.
2018-03-06 Added shortcuts list.
2018-03-06 Updated Hardware and Appendix chapters.
2018-03-06 Added fithesis template example.
2018-03-06 Added figures to thesis.
2018-03-11 LaTeX tables update to tcolorbox.
2018-03-11 Added all remaining chapters.
2018-03-19 Added remaining chapters skeleton to the thesis.
2018-03-19 Bibliograbhy datasheets update.
2018-03-21 Added power supply info to Appendix.
2018-03-21 Added firmware project as PlatformIO.
2018-03-21 Added all PlatformIO help projects to firmware.
2018-03-22 Corrected warnings.
2018-03-22 Added source code of the horse movement analysis.
2018-03-22 Horse Analysis integrated with MPU9250 accelerometer.
2018-03-23 Added conversion of BMP280 raw data to pressure and temperature.
2018-03-23 Fixed bug in FileSystem in constructor initialization. Initialization cannot be done before calling main().
2018-03-23 Added LED control class.
2018-03-23 Added MPU9250 class controlled via I2C.
2018-03-23 WaitForNext function in stopwatch changed.
2018-03-23 Fixed int to float conversion bug in MPU9250 code.
2018-03-23 Added accelerometer output to log and stream with horse analysis.
2018-03-23 Default settings updated.
2018-04-09 MPU9250 magnetometer bugs fixed.
2018-04-09 Thesis text update.
2018-04-09 Created ReadMe.md
2018-04-17 Added FTP server test project.
2018-04-17 Rapidly prototyped WiFi access point with DHCP server, TCP server and basic communication protocol.
2018-04-24 Update thesis, chapter software, usage examples.
2018-04-26 First outdoor test with horses.
2018-04-26 Software chapter completed.
2018-04-27 Restructured firmware folders.
2018-04-28 Restructured files.
2018-04-28 Removed "fi-pdflatex".
2018-04-28 Finished Software chapter in thesis.
2018-04-29 Added Conclusion to the thesis.
2018-04-29 Added UIB thesis clone.
2018-04-29 Corrected mistakes in Abstract.
2018-04-29 UIB clone adapted to this thesis.
2018-04-30 Created draft of Introduction and Conclusion chapters.
2018-04-30 Typographical changes.
2018-04-30 Finished tables in Hardware chapter.
2018-04-30 Added tablet screenshot from measuring to Software chapter.
2018-05-01 Grammar correction.
2018-05-01 UIB thesis clone successfully compiled.
2018-05-04 Typographical changes in the thesis.
2018-05-04 Filled all the biblography.
2018-05-06 Thesis typogragic errors corrected.
2018-05-06 UIB clone of the thesis finished.
2018-05-07 Content of MU thesis and UIB thesis synchronized.
2018-05-08 Thesis update. Only horse analysis chapter remaining.
2018-05-15 Finished Analysis chapter.
2018-05-15 Cloned firmware for Doxygen creation.
2018-05-17 Corrected grammar errors in the thesis.
2018-05-21 Created compilable firmware with makefile.
2018-05-21 Hardware schematics splitted into four sheets.
2018-05-21 Corrected errors in the thesis.
2018-05-30 Added Czech annotation.
2018-05-30 Synchronized UIB clone with the MU version.
2018-06-06 Changed monitor_baud to monitor_speed in platformio.ini.
2018-06-06 Finished paperwork before defense at UIB.
2018-06-06 Added Doxygen folder to .gitignore.

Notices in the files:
hardware/SensorBoard.brd:
CC BY-SA 4.0
parts and their libraries:
esp32: Creative Commons Attribution-ShareAlike 4.0 International
si70xx: (c) 2014 Samuel Lourenço
User-Submitted: Licensing: Creative Commons ShareAlike 4.0 International - https://creativecommons.org/licenses/by-sa/4.0
